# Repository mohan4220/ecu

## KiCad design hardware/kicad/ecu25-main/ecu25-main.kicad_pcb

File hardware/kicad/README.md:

# ECU-25 KiCad project

`ecu25-main/` is the main-board schematic: a KiCad 7 hierarchical project with
one sheet per subsystem. Open `ecu25-main/ecu25-main.kicad_pro` in KiCad.

Component values come from the reviewed calculation sheet in
[docs/circuits/README.md](../../docs/circuits/README.md) — that file is the
design authority; this project is its capture.

## Sheets

| Sheet | Contents |
|-------|----------|
| Power | Input protection (F1, SMCJ16CA, reverse-polarity P-FET), D3+C9 crank hold-up (+12V_HLD), LM5164 buck 12→5 V with a Type-3 ripple-injection network (R7/C10/C11), TLV75533 LDO 5→3.3 V, PTC-protected +12V_SW rail |
| Analog inputs | 3× current-source sender inputs (LM358 + BC857, 8 mA / 2 mA), battery sense ÷5.55, D+ excite + sense |
| AC sensing | 6× ÷235.9 dividers biased at VREF_MID, 3× CT burden + MCP6002 amps, 1.65 V buffered midpoint |
| Digital inputs + MPU | 8× 12 V inputs (divider + BAT54S clamp, per-channel GND-side-switch jumper), MPU → LM2903 comparator with hysteresis |
| Relay drivers | 6× G5LE-1-DC12 + 2N7002K + SS34. All contacts dry: J8 pin 1 OUT_COM is the installer's fused supply, so no field current crosses the board. K5/K6 configurable AUX |
| Comms | TJA1051T/3 CAN (J1939, split termination JP1), THVD1450 RS485 (Modbus RTU, JP2 term), M95M02 EEPROM |
| MCU | STM32F407VGT6, crystals, VCAP, VDDA filter, supercap RTC backup, SWD (TC2030), debug UART |
| Display connector | 20-way ribbon to the display board (SPI + selects + backlight power) |

## MCU pin assignment

ADC: PA0-2 = CT1-3, PA3-7 = oil/fuel/temp/vbat/D+, PC0-5 = gen/mains L1-3.
SPI1 (display) on PB3/4/5, selects PB7/8/9. SPI2 (EEPROM) PB12-15.
CAN1 PD0/PD1. USART3 + DE (RS485) PD8/9/10. USART1 (debug) PA9/10.
Relays PD2-7. Digital inputs PE0-7. TFT RST/INT PE8/9, backlight PWM PE11
(TIM1_CH2). MPU capture PB6 (TIM4_CH1). Heartbeat LED PA8.

## Regenerating

The schematics are generated (and re-generated) by script — do not hand-edit
the `.kicad_sch` files, change the generator instead:

```
.venv/bin/python hardware/kicad/gen/gen_ecu25.py
```

`gen/kisch.py` is the builder library (symbol flattening, pin-exact placement,
wire splitting at T-joins). Validation used during generation:

```
kicad-cli sch export netlist hardware/kicad/ecu25-main/ecu25-main.kicad_sch -o /tmp/ecu25.net
kicad-cli sch export svg hardware/kicad/ecu25-main/ecu25-main.kicad_sch -o /tmp/svgs
```

Run ERC from eeschema (Inspect → Electrical Rules Checker) — kicad-cli 7 has
no ERC command.

## Bill of materials

`gen/gen_bom.py` builds [docs/bom/ecu25-main-bom.md](../../docs/bom/ecu25-main-bom.md)
and the matching CSV from the schematic netlist — 305 parts in 97 order lines,
grouped by orderable value and package. For bench work,
[docs/bom/breadboard-prototype.md](../../docs/bom/breadboard-prototype.md)
translates the SMD design into through-hole blocks that can be built one
subsystem at a time (and explains why the 415 V sensing must not be one of
them). `gen/gen_breadboard_xlsx.py` renders that file as
[docs/bom/ecu25-breadboard-bom.xlsx](../../docs/bom/ecu25-breadboard-bom.xlsx)
— shopping list, one tab per block, safety first.

## PCB

Footprints are assigned in the schematic generator (`footprint_for()` in
`gen_ecu25.py`): 0603 passives by default, wattage/voltage exceptions by value
(1206 AC chain, 1210 0.5 W, 2512 shunts, THT power parts), MKDS-3 terminal
blocks for battery/AC/CT/relay field wiring, MKDS-1,5 for signal-level.

`ecu25-main/ecu25-main.kicad_pcb` is a generated **starting point**, not a
routed board: 200×150 mm 2-layer outline, M3 corner holes, field connectors on
the edges (battery/MPU/D+/senders left, fuse + display ribbon + GEN/MAINS AC
top, CT right, DIN / comms / relay outputs / contactor pairs bottom), relays
in a 2×3 block with the volt-free GEN/MAINS pair above J15, MCU central, buck
hot loop and CT front-ends at fixed positions, remaining parts shelf-packed
inside their subsystem zone, all pads on nets, GND pour both layers with
keepouts under the 415 V regions. J5/J6/J15 are 8-pole blocks with only the
odd poles wired (pad remap in `gen_pcb.py`) — 10.16 mm live pitch for
creepage. Regenerate:

```
kicad-cli sch export netlist hardware/kicad/ecu25-main/ecu25-main.kicad_sch -o /tmp/ecu25.net
python3 hardware/kicad/gen/gen_pcb.py /tmp/ecu25.net   # system python (needs pcbnew)
```

`ecu25-main.kicad_dru` carries the HV clearance rules (3.0 mm for the J5/J6
phase nets and the J15 volt-free contactor nets — GEN and MAINS are
unsynchronized sources, so phase-to-phase can reach ~680 Vpk; 1.0 mm inside
the 4×330k divider chains; per-chain exemptions so the first 330k's own pads
don't false-trip) — pcbnew picks it up automatically. The file is generated:
re-annotating nets by hand orphans the rules, regenerate instead. Routing
guidance: battery input F1→Q1→buck ≥2 mm track; +12V_SW and relay
coil/contact tracks ≥1 mm; 0.05 R CT shunts want wide copper spades and
Kelvin-routed sense off the pad inner edges; VREF_MID is a star net — route
each channel's bias from the buffer side. Interactive routing (or freerouting
via DSN export) is the remaining manual step, then DRC in pcbnew.

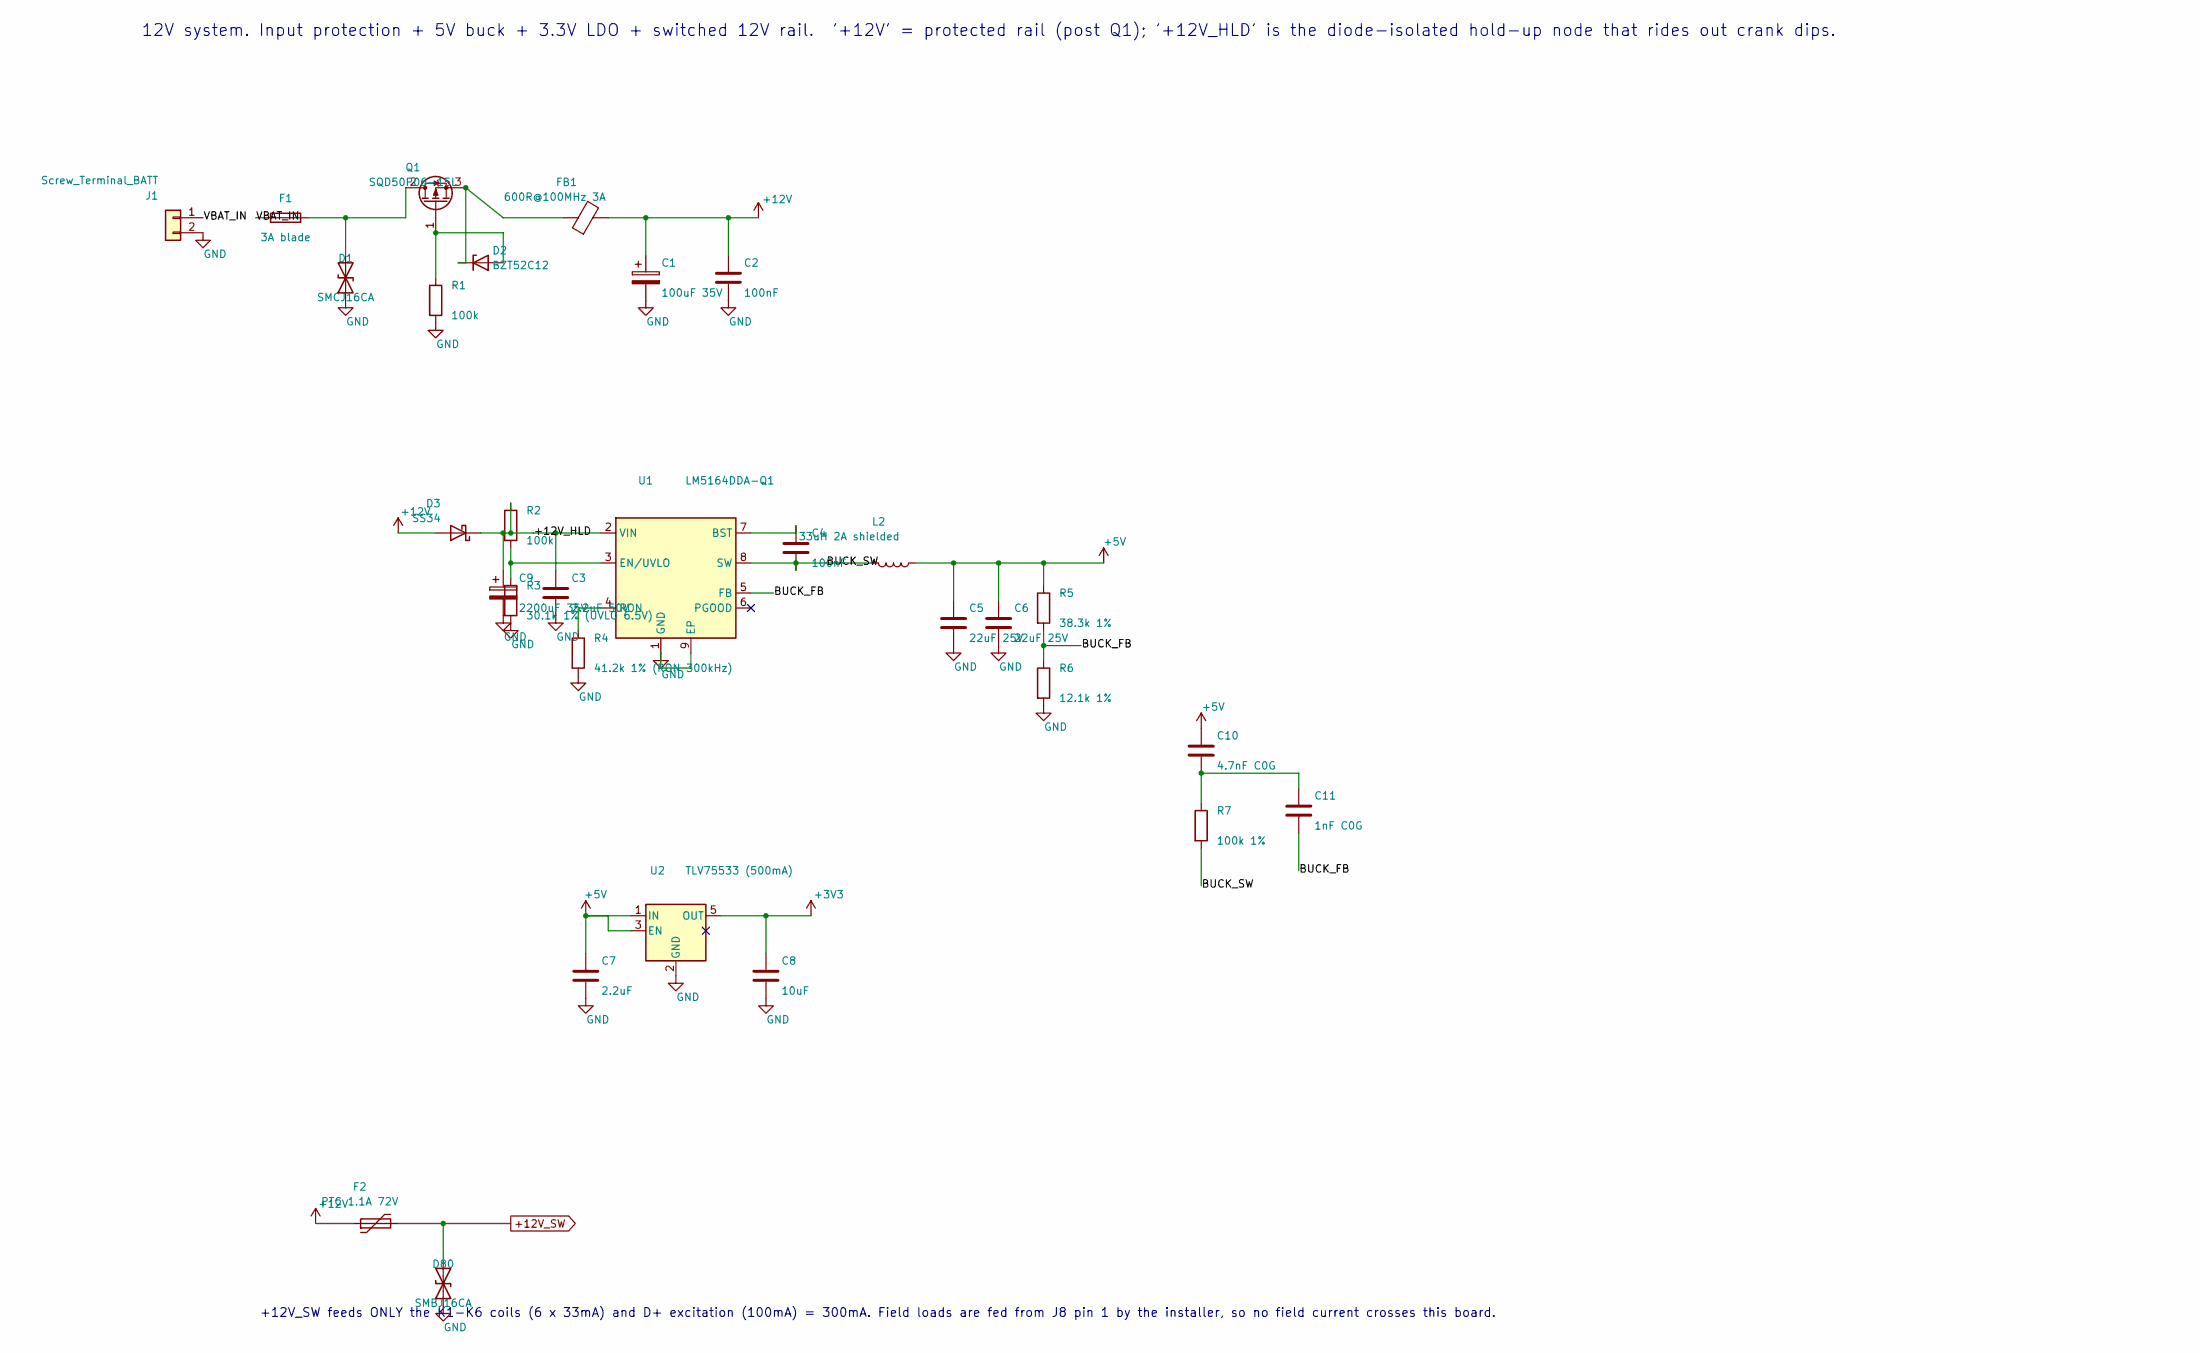
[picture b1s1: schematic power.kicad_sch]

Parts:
C1: 100uF 35V; CP_Radial_D8.0mm_P3.50mm
C2, C4: 100nF; C_0603_1608Metric
C3: 2.2uF 50V; C_1210_3225Metric
C5, C6: 22uF 25V; C_1210_3225Metric
C7: 2.2uF; C_0603_1608Metric
C8: 10uF; C_0805_2012Metric
C9: 2200uF 35V; CP_Radial_D12.5mm_P5.00mm
C10: 4.7nF C0G; C_0603_1608Metric
C11: 1nF C0G; C_0603_1608Metric
D1: SMCJ16CA; D_SMC
D2: BZT52C12; D_SOD-123
D3: SS34; D_SMA
D80: SMBJ16CA; D_SMB
F1: 3A blade; Fuseholder_Blade_Mini_Keystone_3568
F2: PTC 1.1A 72V; Fuse_Bourns_MF-RG900
FB1: 600R@100MHz 3A; L_0805_2012Metric
J1: Screw_Terminal_BATT; TerminalBlock_Phoenix_MKDS-3-2-5.08_1x02_P5.08mm_Horizontal
L2: 33uH 2A shielded; L_12x12mm_H8mm
Q1: SQD50P06-15L; TO-252-2
R1, R2: 100k; R_0603_1608Metric
R3: 30.1k 1% (UVLO 6.5V); R_0603_1608Metric
R4: 41.2k 1% (RON 300kHz); R_0603_1608Metric
R5: 38.3k 1%; R_0603_1608Metric
R6: 12.1k 1%; R_0603_1608Metric
R7: 100k 1%; R_0603_1608Metric
U1: LM5164DDA-Q1; SOIC-8-1EP_3.9x4.9mm_P1.27mm_EP2.514x3.2mm_ThermalVias
U2: TLV75533 (500mA); SOT-23-5

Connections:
+3V3: C8.1, U2.5 (OUT); also elsewhere on the board
+5V: C5.1, C6.1, C7.1, C10.1, L2.1, R5.1, U2.1 (IN), U2.3 (EN); also elsewhere on the board
+12V: C1.1, C2.1, D3.2 (A), F2.1, FB1.2; also elsewhere on the board
+12V_SW: D80.2 (A2), F2.2; also elsewhere on the board
/Power/+12V_HLD: C3.1, C9.1, D3.1 (K), R2.1, U1.2 (VIN)
/Power/BUCK_FB: C11.2, R5.2, R6.1, U1.5 (FB)
/Power/BUCK_SW: C4.2, L2.2, R7.2, U1.8 (SW)
/Power/VBAT_IN: F1.1, J1.1
GND: C1.2, C2.2, C3.2, C5.2, C6.2, C7.2, C8.2, C9.2, D1.1 (A1), D80.1 (A1), J1.2, R1.2, R3.2, R4.2, R6.2, U1.1 (GND), U1.9 (EP), U2.2 (GND); also elsewhere on the board
unnamed: C10.2, C11.1, R7.1
unnamed: D1.2 (A2), F1.2, Q1.2 (D)
unnamed: D2.2 (A), Q1.1 (G), R1.1
unnamed: D2.1 (K), FB1.1, Q1.3 (S)
unnamed: C4.1, U1.7 (BST)
unnamed: R2.2, R3.1, U1.3 (EN/UVLO)
unnamed: R4.1, U1.4 (RON)

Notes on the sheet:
12V system. Input protection + 5V buck + 3.3V LDO + switched 12V rail. '+12V' = protected rail (post Q1); '+12V_HLD' is the diode-isolated hold-up node that rides out crank dips.
+12V_SW feeds ONLY the K1-K6 coils (6 x 33mA) and D+ excitation (100mA) = 300mA. Field loads are fed from J8 pin 1 by the installer, so no field current crosses this board.

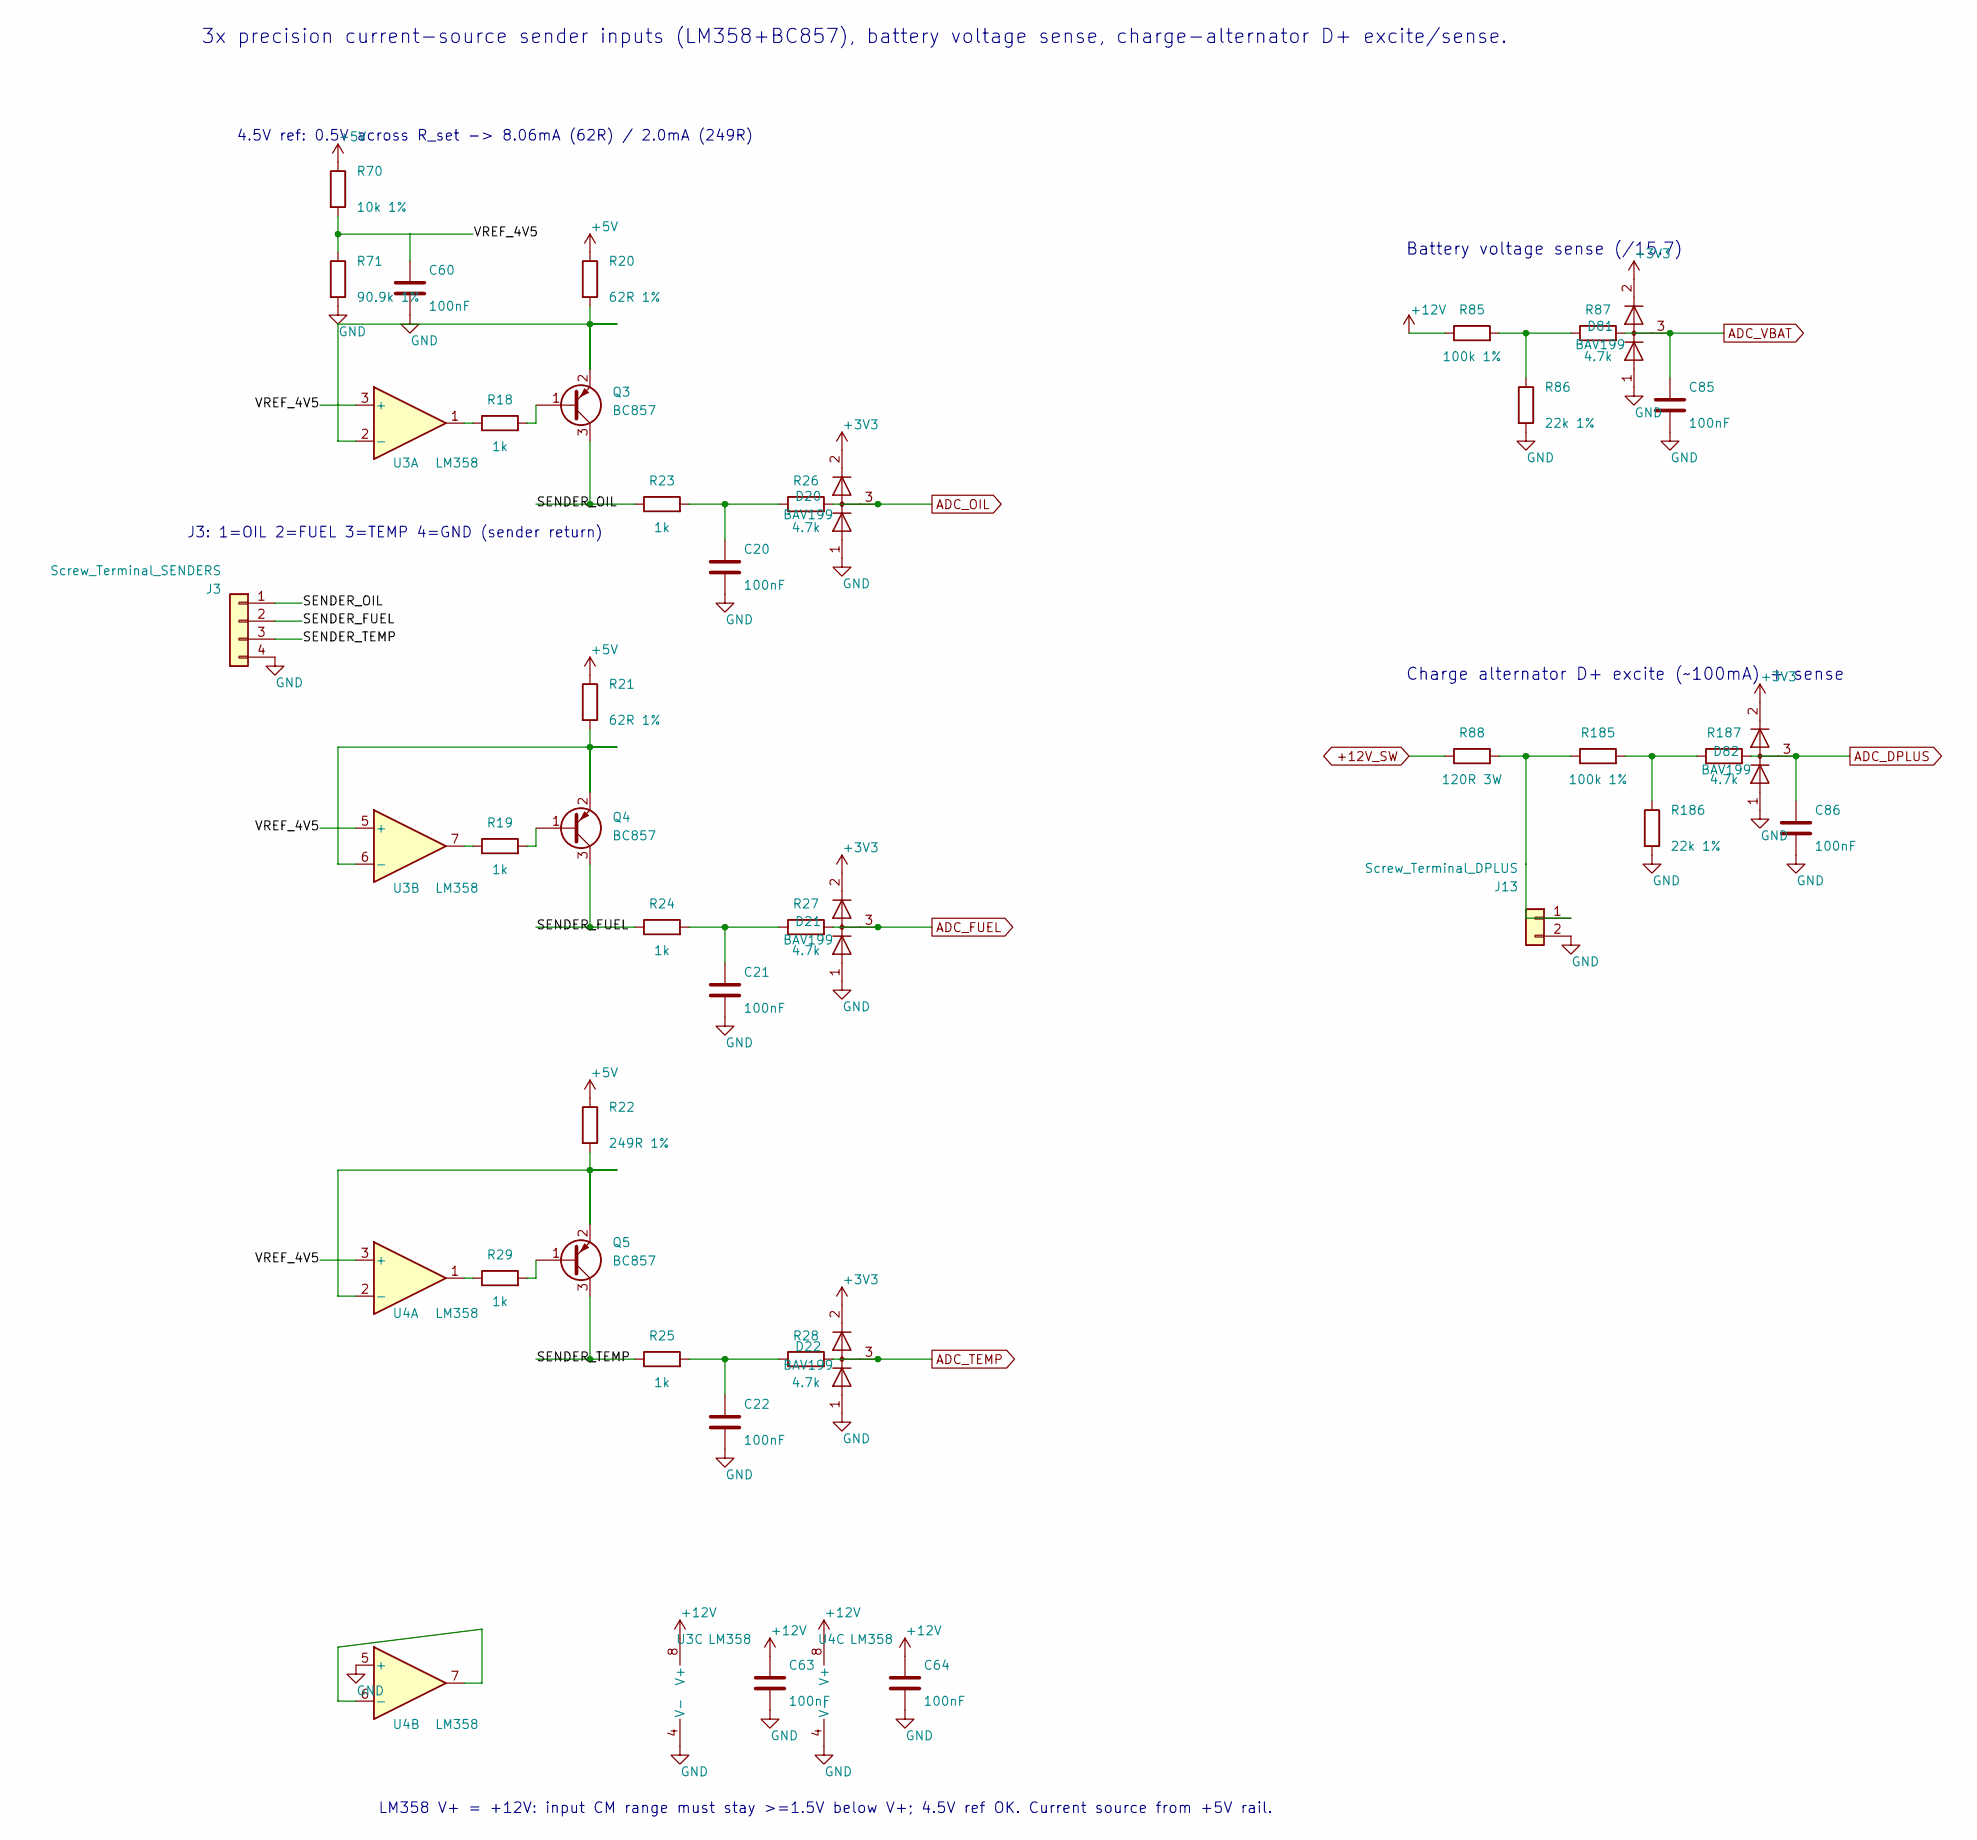
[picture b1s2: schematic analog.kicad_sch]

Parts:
C20, C21, C22, C60, C63, C64, C85, C86: 100nF; C_0603_1608Metric
D20, D21, D22, D81, D82: BAV199; SOT-23
J3: Screw_Terminal_SENDERS; TerminalBlock_Phoenix_MKDS-1,5-4-5.08_1x04_P5.08mm_Horizont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
J13: Screw_Terminal_DPLUS; TerminalBlock_Phoenix_MKDS-1,5-2-5.08_1x02_P5.08mm_Horizont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
Q3, Q4, Q5: BC857; SOT-23
R18, R19, R23, R24, R25, R29: 1k; R_0603_1608Metric
R20, R21: 62R 1%; R_0603_1608Metric
R22: 249R 1%; R_0603_1608Metric
R26, R27, R28, R87, R187: 4.7k; R_0603_1608Metric
R70: 10k 1%; R_0603_1608Metric
R71: 90.9k 1%; R_0603_1608Metric
R85, R185: 100k 1%; R_0603_1608Metric
R86, R186: 22k 1%; R_0603_1608Metric
R88: 120R 3W; R_Axial_Power_L20.0mm_W6.4mm_P25.40mm
U3, U4: LM358; SOIC-8_3.9x4.9mm_P1.27mm

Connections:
+3V3: D20.2 (A), D21.2 (A), D22.2 (A), D81.2 (A), D82.2 (A); also elsewhere on the board
+5V: R20.1, R21.1, R22.1, R70.1; also elsewhere on the board
+12V: C63.1, C64.1, R85.1, U3.8 (V+), U4.8 (V+); also elsewhere on the board
+12V_SW: R88.1; also elsewhere on the board
/Analog inputs/SENDER_FUEL: J3.2, Q4.3 (C), R24.1
/Analog inputs/SENDER_OIL: J3.1, Q3.3 (C), R23.1
/Analog inputs/SENDER_TEMP: J3.3, Q5.3 (C), R25.1
/Analog inputs/VREF_4V5: C60.1, R70.2, R71.1, U3.3 (+), U3.5 (+), U4.3 (+)
ADC_DPLUS: C86.1, D82.3 (K), R187.2; also elsewhere on the board
ADC_FUEL: D21.3 (K), R27.2; also elsewhere on the board
ADC_OIL: D20.3 (K), R26.2; also elsewhere on the board
ADC_TEMP: D22.3 (K), R28.2; also elsewhere on the board
ADC_VBAT: C85.1, D81.3 (K), R87.2; also elsewhere on the board
GND: C20.2, C21.2, C22.2, C60.2, C63.2, C64.2, C85.2, C86.2, D20.1 (K), D21.1 (K), D22.1 (K), D81.1 (K), D82.1 (K), J3.4, J13.2, R71.2, R86.2, R186.2, U3.4 (V-), U4.4 (V-), U4.5 (+); also elsewhere on the board
unnamed: C20.1, R23.2, R26.1
unnamed: C21.1, R24.2, R27.1
unnamed: C22.1, R25.2, R28.1
unnamed: J13.1, R88.2, R185.1
unnamed: Q3.1 (B), R18.2
unnamed: Q3.2 (E), R20.2, U3.2 (-)
unnamed: Q4.1 (B), R19.2
unnamed: Q4.2 (E), R21.2, U3.6 (-)
unnamed: Q5.1 (B), R29.2
unnamed: Q5.2 (E), R22.2, U4.2 (-)
unnamed: R18.1, U3.1
unnamed: R19.1, U3.7
unnamed: R29.1, U4.1
unnamed: R85.2, R86.1, R87.1
unnamed: R185.2, R186.1, R187.1
unnamed: U4.6 (-), U4.7

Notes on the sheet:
3x precision current-source sender inputs (LM358+BC857), battery voltage sense, charge-alternator D+ excite/sense.
4.5V ref: 0.5V across R_set -> 8.06mA (62R) / 2.0mA (249R)
J3: 1=OIL 2=FUEL 3=TEMP 4=GND (sender return)
LM358 V+ = +12V: input CM range must stay >=1.5V below V+; 4.5V ref OK. Current source from +5V rail.
Battery voltage sense (/15.7)
Charge alternator D+ excite (~100mA) + sense

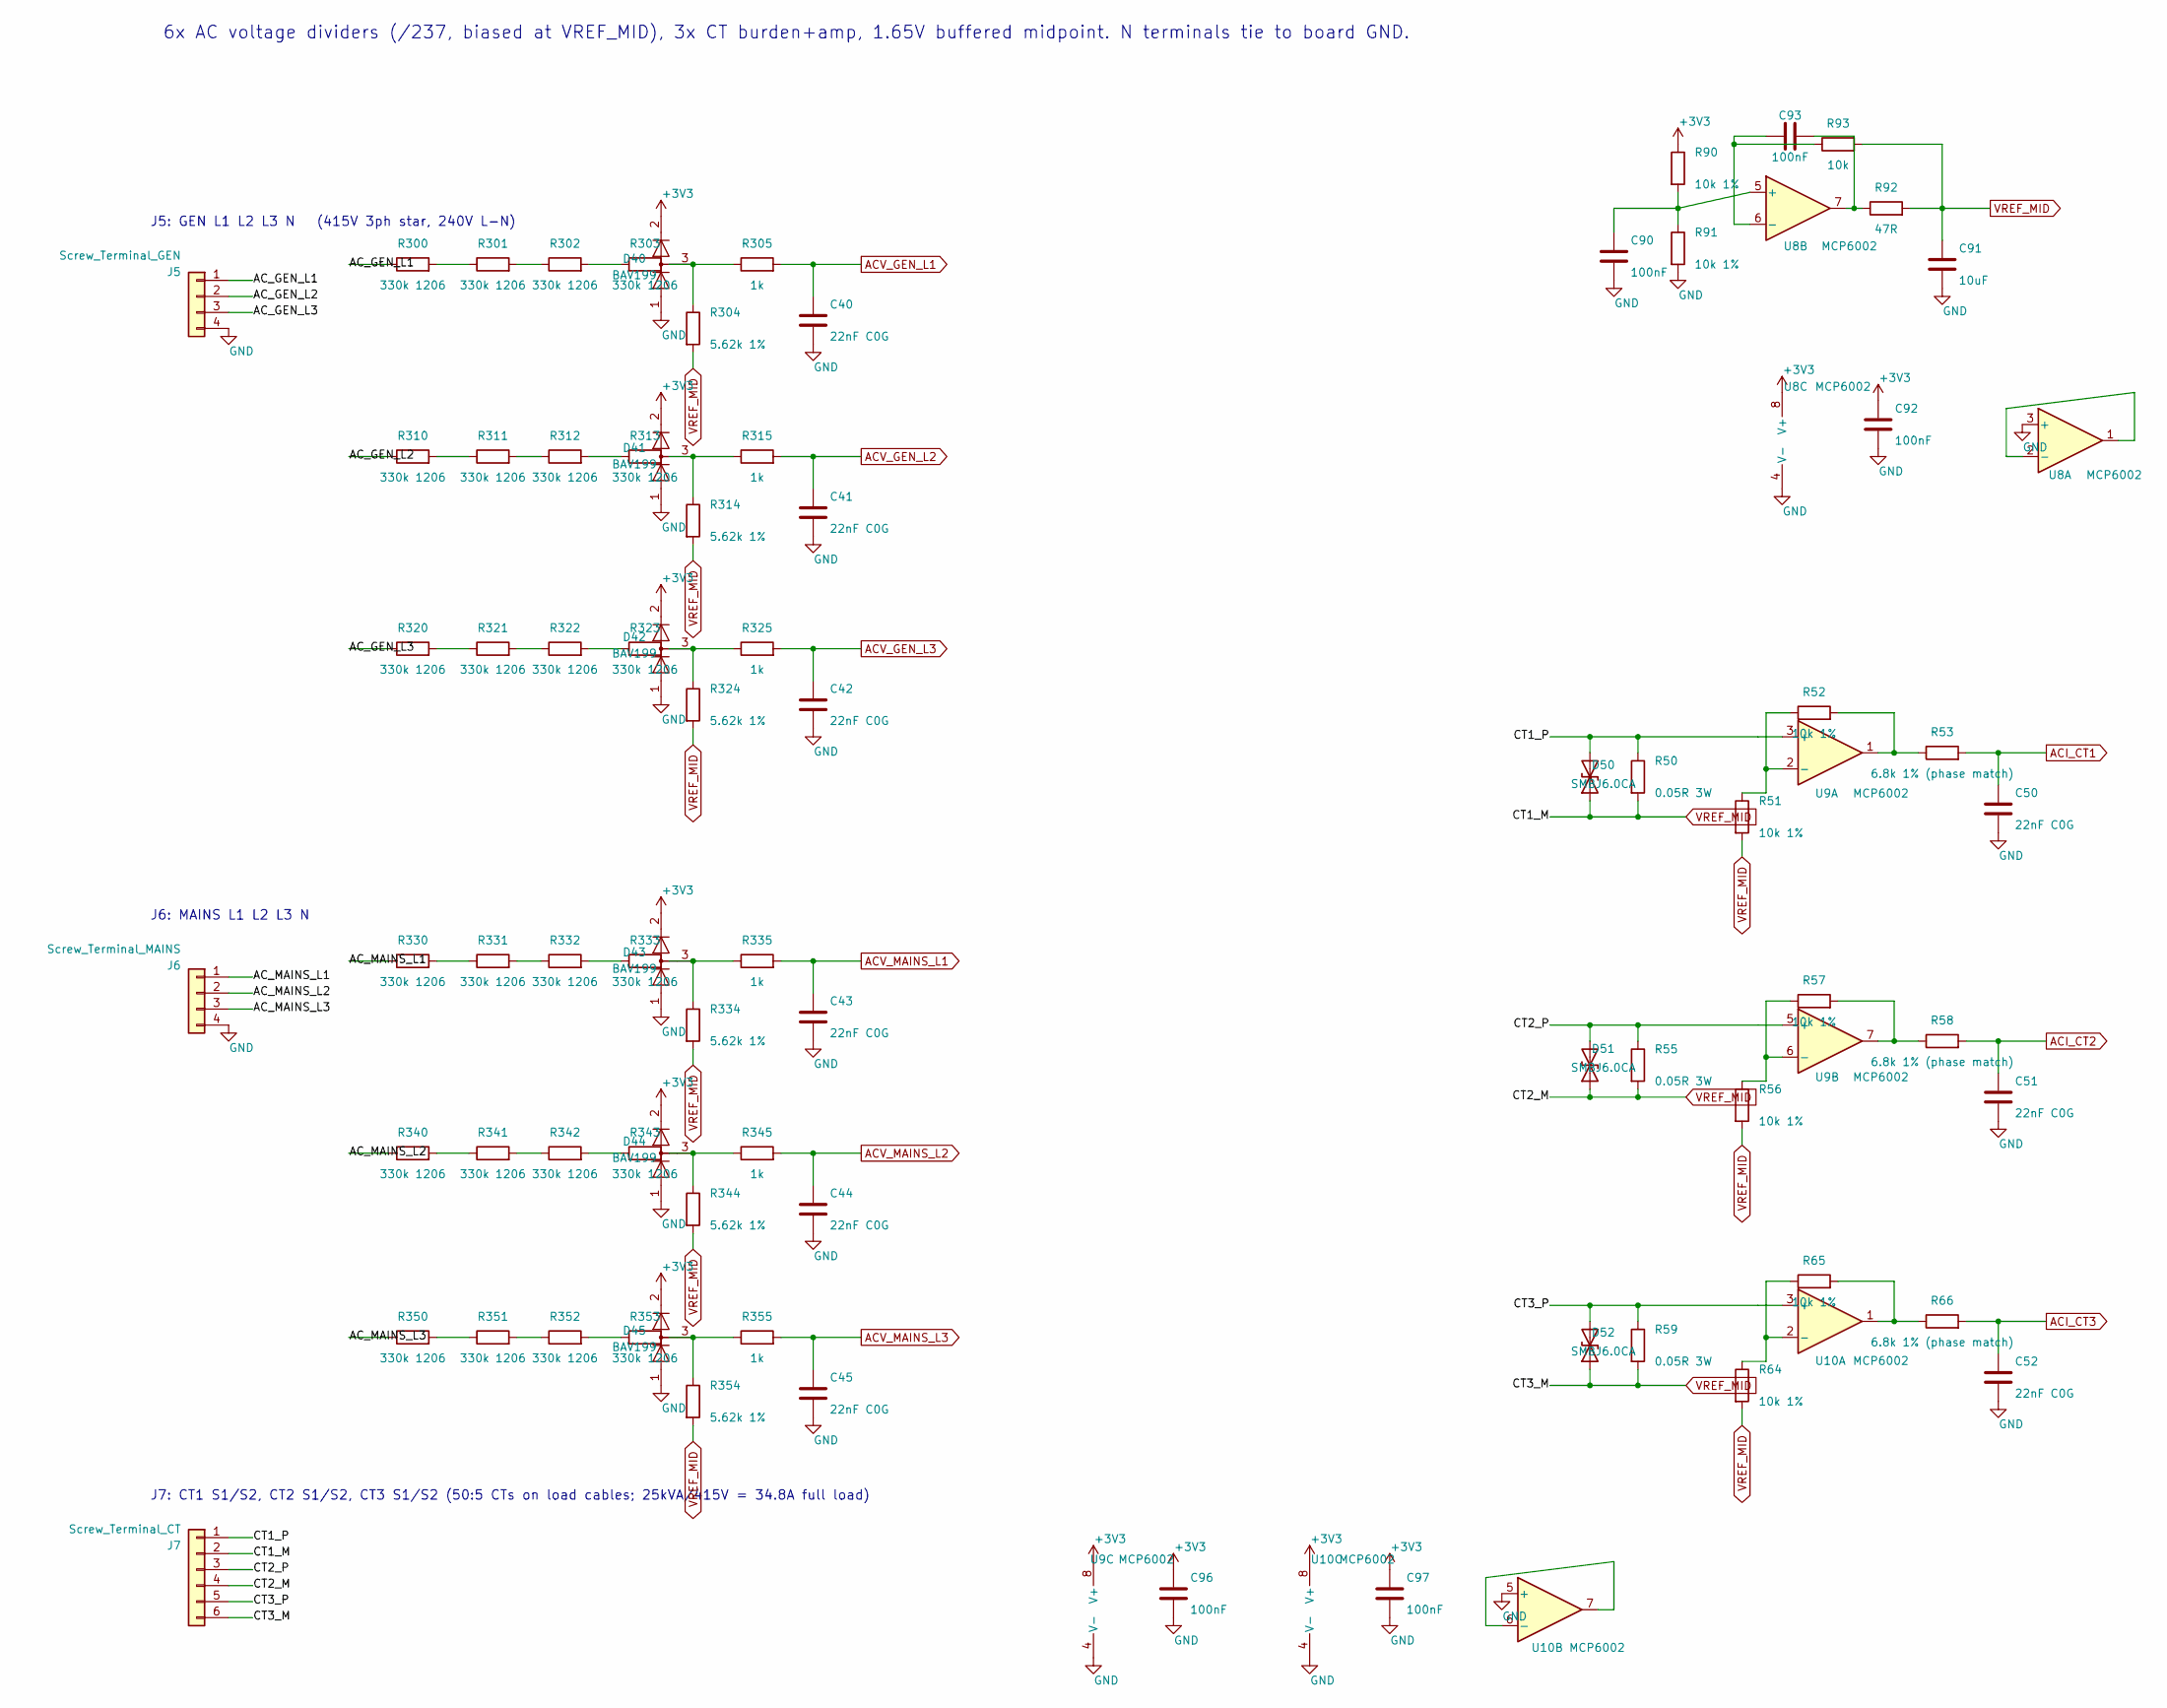
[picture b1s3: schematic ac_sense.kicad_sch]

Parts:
C40, C41, C42, C43, C44, C45, C50, C51, C52: 22nF C0G; C_0603_1608Metric
C90, C92, C93, C96, C97: 100nF; C_0603_1608Metric
C91: 10uF; C_0805_2012Metric
D40, D41, D42, D43, D44, D45: BAV199; SOT-23
D50, D51, D52: SMBJ6.0CA; D_SMB
J5: Screw_Terminal_GEN; TerminalBlock_Phoenix_MKDS-3-8-5.08_1x08_P5.08mm_Horizontal
J6: Screw_Terminal_MAINS; TerminalBlock_Phoenix_MKDS-3-8-5.08_1x08_P5.08mm_Horizontal
J7: Screw_Terminal_CT; TerminalBlock_Phoenix_MKDS-3-6-5.08_1x06_P5.08mm_Horizontal
R50, R55, R59: 0.05R 3W; R_2512_6332Metric
R51, R52, R56, R57, R64, R65, R90, R91: 10k 1%; R_0603_1608Metric
R53, R58, R66: 6.8k 1% (phase match); R_0603_1608Metric
R92: 47R; R_0603_1608Metric
R93: 10k; R_0603_1608Metric
R300, R301, R302, R303, R310, R311, R312, R313, R320, R321, R322, R323, R330, R331, R332, R333, R340, R341, R342, R343, R350, R351, R352, R353: 330k 1206; R_1206_3216Metric
R304, R314, R324, R334, R344, R354: 5.62k 1%; R_0603_1608Metric
R305, R315, R325, R335, R345, R355: 1k; R_0603_1608Metric
U8, U9, U10: MCP6002; SOIC-8_3.9x4.9mm_P1.27mm

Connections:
+3V3: C92.1, C96.1, C97.1, D40.2 (A), D41.2 (A), D42.2 (A), D43.2 (A), D44.2 (A), D45.2 (A), R90.1, U8.8 (V+), U9.8 (V+), U10.8 (V+); also elsewhere on the board
/AC sensing/AC_GEN_L1: J5.1, R300.1
/AC sensing/AC_MAINS_L1: J6.1, R330.1
/AC sensing/CT1_P: D50.2 (A2), J7.1, R50.1, U9.3 (+)
/AC sensing/CT2_P: D51.2 (A2), J7.3, R55.1, U9.5 (+)
/AC sensing/CT3_P: D52.2 (A2), J7.5, R59.1, U10.3 (+)
ACI_CT1: C50.1, R53.2; also elsewhere on the board
ACI_CT2: C51.1, R58.2; also elsewhere on the board
ACI_CT3: C52.1, R66.2; also elsewhere on the board
ACV_GEN_L1: C40.1, R305.2; also elsewhere on the board
ACV_GEN_L2: C41.1, R315.2; also elsewhere on the board
ACV_GEN_L3: C42.1, R325.2; also elsewhere on the board
ACV_MAINS_L1: C43.1, R335.2; also elsewhere on the board
ACV_MAINS_L2: C44.1, R345.2; also elsewhere on the board
ACV_MAINS_L3: C45.1, R355.2; also elsewhere on the board
GND: C40.2, C41.2, C42.2, C43.2, C44.2, C45.2, C50.2, C51.2, C52.2, C90.2, C91.2, C92.2, C96.2, C97.2, D40.1 (K), D41.1 (K), D42.1 (K), D43.1 (K), D44.1 (K), D45.1 (K), J5.4, J5.7, J6.4, J6.7, R91.2, U8.3 (+), U8.4 (V-), U9.4 (V-), U10.4 (V-), U10.5 (+); also elsewhere on the board
unnamed: C93.2, R92.1, U8.7
unnamed: D40.3 (K), R303.2, R304.1, R305.1
unnamed: D41.3 (K), R313.2, R314.1, R315.1
unnamed: D42.3 (K), R323.2, R324.1, R325.1
unnamed: D43.3 (K), R333.2, R334.1, R335.1
unnamed: D44.3 (K), R343.2, R344.1, R345.1
unnamed: D45.3 (K), R353.2, R354.1, R355.1
unnamed: R52.2, R53.1, U9.1
unnamed: R57.2, R58.1, U9.7
unnamed: R65.2, R66.1, U10.1
unnamed: R300.2, R301.1
unnamed: R301.2, R302.1
unnamed: R302.2, R303.1
unnamed: R310.2, R311.1
unnamed: R311.2, R312.1
unnamed: R312.2, R313.1
unnamed: R320.2, R321.1
unnamed: R321.2, R322.1
unnamed: R322.2, R323.1
unnamed: R330.2, R331.1
unnamed: R331.2, R332.1
unnamed: R332.2, R333.1
unnamed: R340.2, R341.1
unnamed: R341.2, R342.1
unnamed: R342.2, R343.1
unnamed: R350.2, R351.1
unnamed: R351.2, R352.1
unnamed: R352.2, R353.1
unnamed: U8.1, U8.2 (-)
unnamed: C90.1, R90.2, R91.1, U8.5 (+)
unnamed: C93.1, R93.1, U8.6 (-)
unnamed: R51.1, R52.1, U9.2 (-)
unnamed: R56.1, R57.1, U9.6 (-)
unnamed: R64.1, R65.1, U10.2 (-)
unnamed: U10.6 (-), U10.7
VREF_MID: C91.1, D50.1 (A1), D51.1 (A1), D52.1 (A1), J7.2, J7.4, J7.6, R50.2, R51.2, R55.2, R56.2, R59.2, R64.2, R92.2, R93.2, R304.2, R314.2, R324.2, R334.2, R344.2, R354.2

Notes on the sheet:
6x AC voltage dividers (/237, biased at VREF_MID), 3x CT burden+amp, 1.65V buffered midpoint. N terminals tie to board GND.
J5: GEN L1 L2 L3 N (415V 3ph star, 240V L-N)
J6: MAINS L1 L2 L3 N
J7: CT1 S1/S2, CT2 S1/S2, CT3 S1/S2 (50:5 CTs on load cables; 25kVA/415V = 34.8A full load)

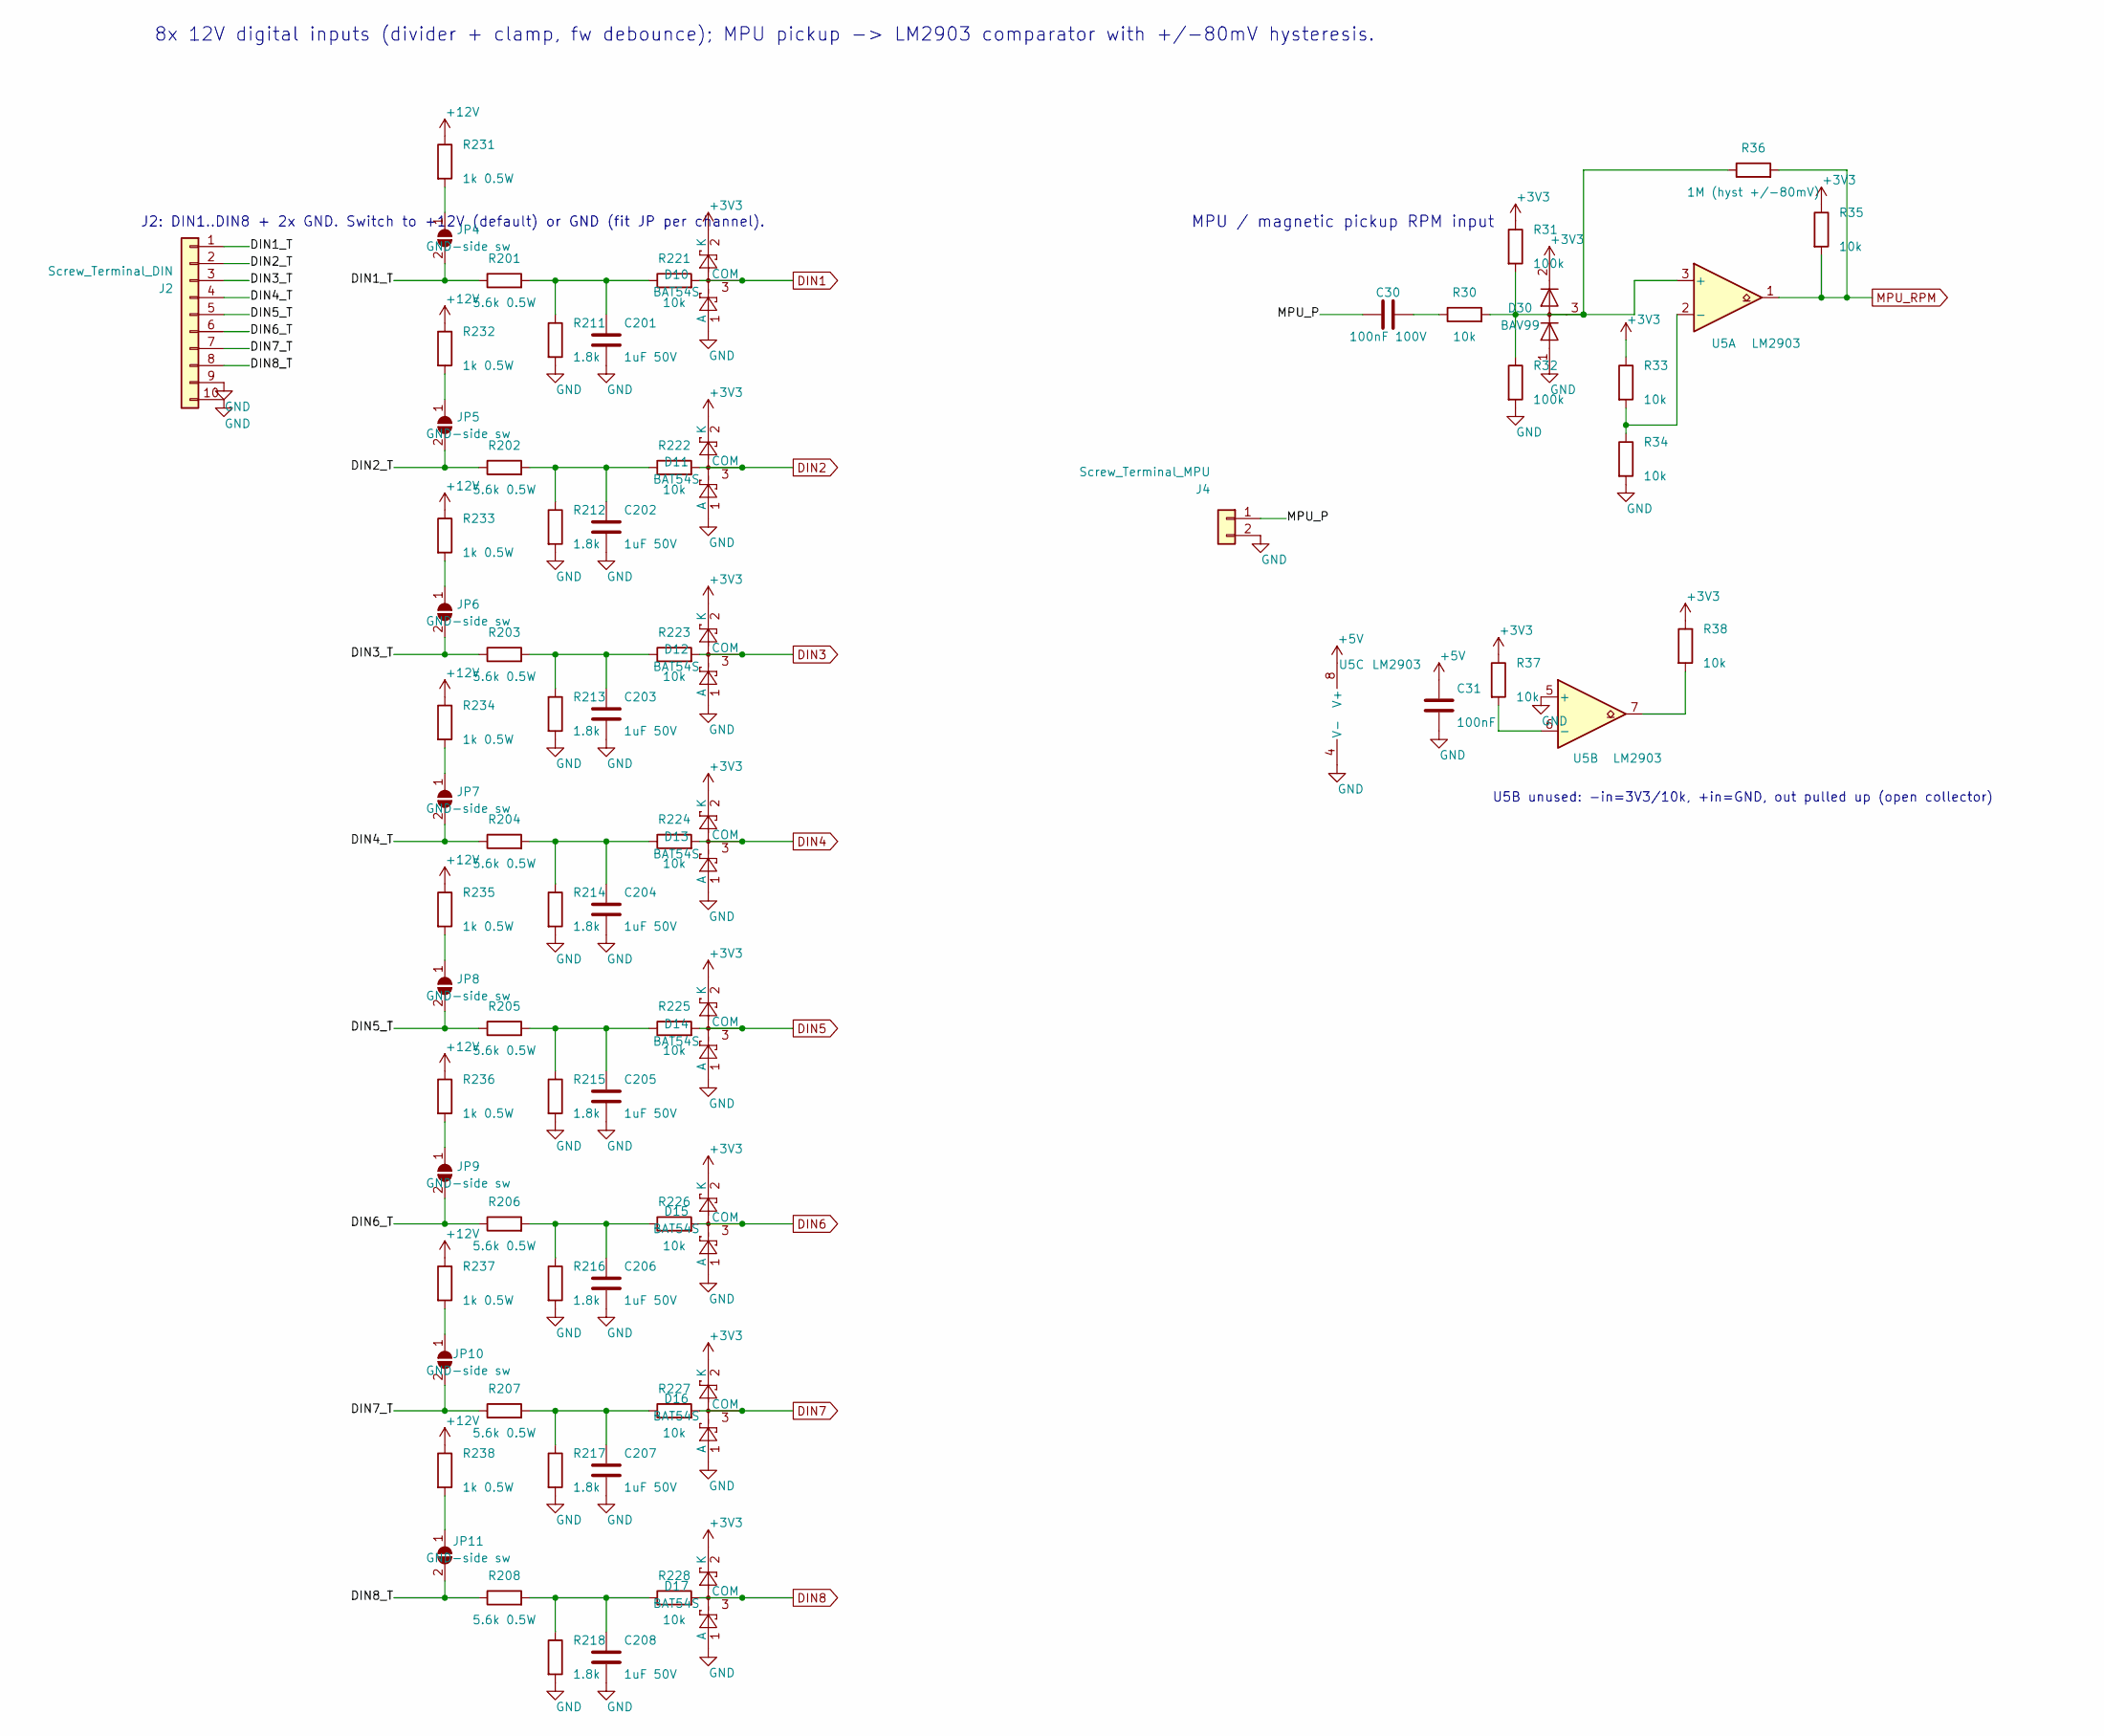
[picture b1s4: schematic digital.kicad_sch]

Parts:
C30: 100nF 100V; C_0805_2012Metric
C31: 100nF; C_0603_1608Metric
C201, C202, C203, C204, C205, C206, C207, C208: 1uF 50V; C_0603_1608Metric
D10, D11, D12, D13, D14, D15, D16, D17: BAT54S; SOT-23
D30: BAV99; SOT-23
J2: Screw_Terminal_DIN; TerminalBlock_Phoenix_MKDS-1,5-10-5.08_1x10_P5.08mm_Horizon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
J4: Screw_Terminal_MPU; TerminalBlock_Phoenix_MKDS-1,5-2-5.08_1x02_P5.08mm_Horizont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
JP4, JP5, JP6, JP7, JP8, JP9, JP10, JP11: GND-side sw; SolderJumper-2_P1.3mm_Open_RoundedPad1.0x1.5mm
R30, R33, R34, R35, R37, R38, R221, R222, R223, R224, R225, R226, R227, R228: 10k; R_0603_1608Metric
R31, R32: 100k; R_0603_1608Metric
R36: 1M (hyst +/-80mV); R_0603_1608Metric
R201, R202, R203, R204, R205, R206, R207, R208: 5.6k 0.5W; R_1210_3225Metric
R211, R212, R213, R214, R215, R216, R217, R218: 1.8k; R_0603_1608Metric
R231, R232, R233, R234, R235, R236, R237, R238: 1k 0.5W; R_1210_3225Metric
U5: LM2903; SOIC-8_3.9x4.9mm_P1.27mm

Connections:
+3V3: D10.2 (K), D11.2 (K), D12.2 (K), D13.2 (K), D14.2 (K), D15.2 (K), D16.2 (K), D17.2 (K), D30.2 (A), R31.1, R33.1, R35.1, R37.1, R38.1; also elsewhere on the board
+5V: C31.1, U5.8 (V+); also elsewhere on the board
+12V: R231.1, R232.1, R233.1, R234.1, R235.1, R236.1, R237.1, R238.1; also elsewhere on the board
/Digital inputs + MPU/DIN1_T: J2.1, JP4.2 (B), R201.1
/Digital inputs + MPU/DIN2_T: J2.2, JP5.2 (B), R202.1
/Digital inputs + MPU/DIN3_T: J2.3, JP6.2 (B), R203.1
/Digital inputs + MPU/DIN4_T: J2.4, JP7.2 (B), R204.1
/Digital inputs + MPU/DIN5_T: J2.5, JP8.2 (B), R205.1
/Digital inputs + MPU/DIN6_T: J2.6, JP9.2 (B), R206.1
/Digital inputs + MPU/DIN7_T: J2.7, JP10.2 (B), R207.1
/Digital inputs + MPU/DIN8_T: J2.8, JP11.2 (B), R208.1
/Digital inputs + MPU/MPU_P: C30.1, J4.1
DIN1: D10.3 (COM), R221.2; also elsewhere on the board
DIN2: D11.3 (COM), R222.2; also elsewhere on the board
DIN3: D12.3 (COM), R223.2; also elsewhere on the board
DIN4: D13.3 (COM), R224.2; also elsewhere on the board
DIN5: D14.3 (COM), R225.2; also elsewhere on the board
DIN6: D15.3 (COM), R226.2; also elsewhere on the board
DIN7: D16.3 (COM), R227.2; also elsewhere on the board
DIN8: D17.3 (COM), R228.2; also elsewhere on the board
GND: C31.2, C201.2, C202.2, C203.2, C204.2, C205.2, C206.2, C207.2, C208.2, D10.1 (A), D11.1 (A), D12.1 (A), D13.1 (A), D14.1 (A), D15.1 (A), D16.1 (A), D17.1 (A), D30.1 (K), J2.9, J2.10, J4.2, R32.2, R34.2, R211.2, R212.2, R213.2, R214.2, R215.2, R216.2, R217.2, R218.2, U5.4 (V-), U5.5 (+); also elsewhere on the board
MPU_RPM: R35.2, R36.2, U5.1; also elsewhere on the board
unnamed: C30.2, R30.1
unnamed: C201.1, R201.2, R211.1, R221.1
unnamed: C202.1, R202.2, R212.1, R222.1
unnamed: C203.1, R203.2, R213.1, R223.1
unnamed: C204.1, R204.2, R214.1, R224.1
unnamed: C205.1, R205.2, R215.1, R225.1
unnamed: C206.1, R206.2, R216.1, R226.1
unnamed: C207.1, R207.2, R217.1, R227.1
unnamed: C208.1, R208.2, R218.1, R228.1
unnamed: JP4.1 (A), R231.2
unnamed: JP5.1 (A), R232.2
unnamed: JP6.1 (A), R233.2
unnamed: JP7.1 (A), R234.2
unnamed: JP8.1 (A), R235.2
unnamed: JP9.1 (A), R236.2
unnamed: JP10.1 (A), R237.2
unnamed: JP11.1 (A), R238.2
unnamed: R38.2, U5.7
unnamed: D30.3 (K), R30.2, R31.2, R32.1, R36.1, U5.3 (+)
unnamed: R33.2, R34.1, U5.2 (-)
unnamed: R37.2, U5.6 (-)

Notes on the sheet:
8x 12V digital inputs (divider + clamp, fw debounce); MPU pickup -> LM2903 comparator with +/-80mV hysteresis.
J2: DIN1..DIN8 + 2x GND. Switch to +12V (default) or GND (fit JP per channel).
MPU / magnetic pickup RPM input
U5B unused: -in=3V3/10k, +in=GND, out pulled up (open collector)
